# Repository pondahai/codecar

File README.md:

# codecar
programable toy car, Arduino + TAMIYA

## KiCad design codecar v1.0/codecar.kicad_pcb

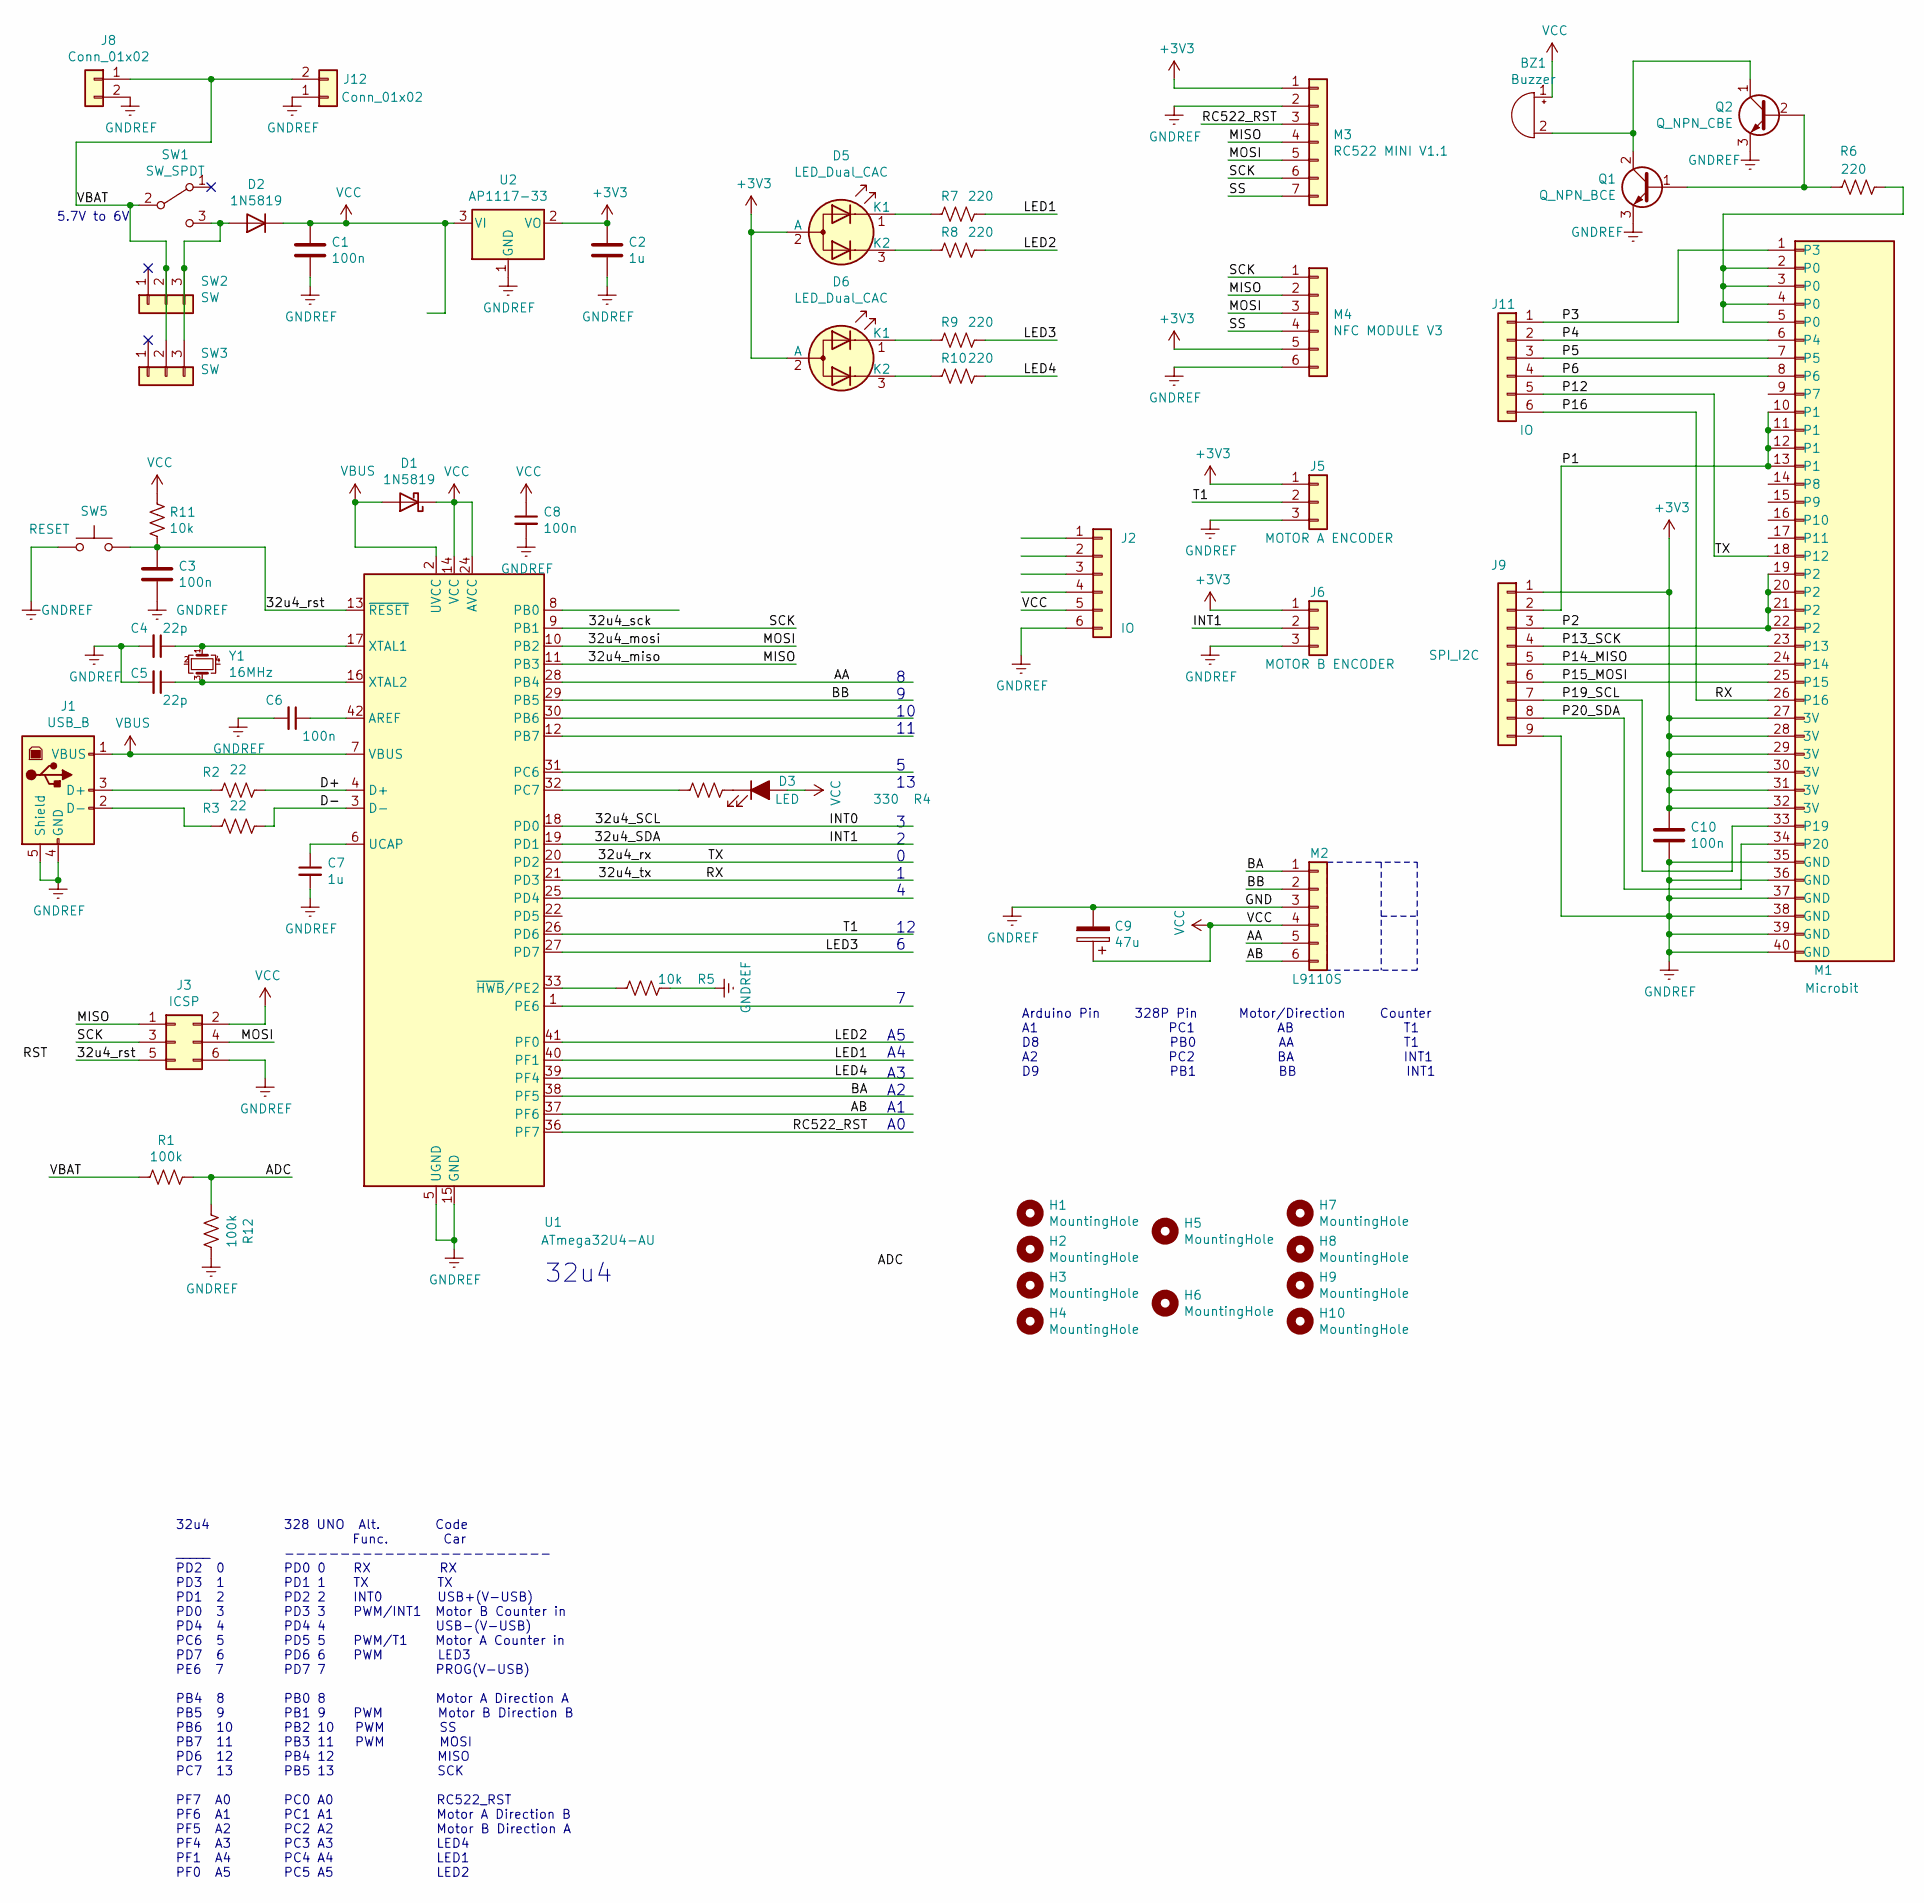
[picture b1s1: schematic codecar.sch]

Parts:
BZ1: Buzzer; Buzzer_12x9.5RM7.6
C1, C10: 100n; CP_EIA-2012-12_Kemet-R_Pad1.30x1.05mm_HandSolder
C2: 1u; C_Radial_D8.0mm_H7.0mm_P3.50mm
C3: 100n; CP_EIA-3216-10_Kemet-I_Pad1.58x1.35mm_HandSolder
C4, C5: 22p; C_0805_2012Metric
C6, C8: 100n; C_0805_2012Metric
C7: 1u; CP_EIA-3216-10_Kemet-I_Pad1.58x1.35mm_HandSolder
C9: 47u; C_Radial_D8.0mm_H7.0mm_P3.50mm
D1, D2: 1N5819; D_DO-41_SOD81_P10.16mm_Horizontal
D3: LED; LED_0805_2012Metric
D5, D6: LED_Dual_CAC; LED_D3.0mm-3
H1, H2, H3, H4: MountingHole; MountingHole_3.2mm_M3
H5, H6: MountingHole; MountingHole_4.3mm_M4
H7, H8, H9, H10: MountingHole; MountingHole_2.2mm_M2
J1: USB_B; USB_B_Lumberg_2411_02_Horizontal
J2, J11: IO; PinHeader_1x06_P2.54mm_Vertical
J3: ICSP; PinHeader_2x03_P2.54mm_Vertical
J5: MOTOR A ENCODER; TerminalBlock_Phoenix_MKDS-1,5-3_1x03_P5.00mm_Horizontal
J6: MOTOR B ENCODER; TerminalBlock_Phoenix_MKDS-1,5-3_1x03_P5.00mm_Horizontal
J8: Conn_01x02; Molex_KK-254_AE-6410-02A_1x02_P2.54mm_Vertical
J9: SPI_I2C; PinHeader_1x09_P2.54mm_Vertical
J12: Conn_01x02; TerminalBlock_Phoenix_MKDS-1,5-2_1x02_P5.00mm_Horizontal
M1: Microbit
M2: L9110S
M3: RC522 MINI V1.1; PinHeader_1x07_P2.54mm_Vertical
M4: NFC MODULE V3; PinHeader_1x06_P2.54mm_Vertical
Q1: Q_NPN_BCE; TO-92L_Inline_Wide
Q2: Q_NPN_CBE; TO-92L_Inline_Wide
R1, R12: 100k; R_0805_2012Metric
R2, R3: 22; R_0805_2012Metric
R4: 330; R_0805_2012Metric
R5: 10k; R_0805_2012Metric
R6: 220; R_0805_2012Metric
R7, R8, R9, R10: 220; R_0805_2012Metric_Pad1.20x1.40mm_HandSolder
R11: 10k; R_0805_2012Metric_Pad1.20x1.40mm_HandSolder
SW1: SW_SPDT; SW_Slide_1P2T_CK_OS102011MS2Q
SW2, SW3: SW; PinHeader_1x03_P2.54mm_Vertical
SW5: RESET; SW_PUSH_6mm_H5mm
U1: ATmega32U4-AU; TQFP-44_10x10mm_P0.8mm
U2: AP1117-33; SOT-223-3_TabPin2
Y1: 16MHz; Crystal_SMD_0603-4Pin_6.0x3.5mm_HandSoldering

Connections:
+3V3: C2.1, C10.1, D5.2 (A), D6.2 (A), J5.1, J6.1, J9.1, M1.27 (3V), M1.28 (3V), M1.29 (3V), M1.30 (3V), M1.31 (3V), M1.32 (3V), M3.1, M4.5, U2.2 (VO)
/32u4_SDA: J6.2, U1.19 (PD1)
/32u4_miso: J3.1, M3.4, M4.2, U1.11 (PB3)
/32u4_mosi: J3.4, M3.5, M4.3, U1.10 (PB2)
/32u4_rst: C3.1, J3.5, R11.2, SW5.2, U1.13 (~RESET)
/32u4_rx: J11.5, M1.18 (P12), U1.20 (PD2)
/32u4_sck: J3.3, M3.6, M4.1, U1.9 (PB1)
/32u4_tx: J11.6, M1.26 (P16), U1.21 (PD3)
/AA: M2.5, U1.28 (PB4)
/AB: M2.6, U1.37 (PF6)
/ADC: R1.1, R12.2
/BA: M2.1, U1.38 (PF5)
/BB: M2.2, U1.29 (PB5)
/D+: R2.1, U1.4 (D+)
/D-: R3.1, U1.3 (D-)
/LED1: R7.1, U1.40 (PF1)
/LED2: R8.1, U1.41 (PF0)
/LED3: R9.1, U1.27 (PD7)
/LED4: R10.1, U1.39 (PF4)
/P1: J9.2, M1.10 (P1), M1.11 (P1), M1.12 (P1), M1.13 (P1)
/P2: J9.3, M1.19 (P2), M1.20 (P2), M1.21 (P2), M1.22 (P2)
/P3: J11.1, M1.1 (P3)
/P4: J11.2, M1.6 (P4)
/P5: J11.3, M1.7 (P5)
/P6: J11.4, M1.8 (P6)
/P13_SCK: J9.4, M1.23 (P13)
/P14_MISO: J9.5, M1.24 (P14)
/P15_MOSI: J9.6, M1.25 (P15)
/P19_SCL: J9.7, M1.33 (P19)
/P20_SDA: J9.8, M1.34 (P20)
/RC522_RST: M3.3, U1.36 (PF7)
/SS: M3.7, M4.4
/T1: J5.2, U1.26 (PD6)
/VBAT: J8.1, J12.2, R1.2, SW1.2 (B), SW2.2, SW3.2
GNDREF: C1.2, C2.2, C3.2, C4.2, C5.2, C6.2, C7.2, C8.2, C9.2, C10.2, J1.4 (GND), J1.5 (Shield), J2.6, J3.6, J5.3, J6.3, J8.2, J9.9, J12.1, M1.35 (GND), M1.36 (GND), M1.37 (GND), M1.38 (GND), M1.39 (GND), M1.40 (GND), M2.3, M3.2, M4.6, Q1.3 (E), Q2.3 (E), R5.2, R12.1, SW5.1, U1.5 (UGND), U1.15 (GND), U1.23 (GND), U1.35 (GND), U1.43 (GND), U2.1 (GND)
unnamed: BZ1.2 (+), Q1.2 (C), Q2.1 (C)
unnamed: C4.1, U1.17 (XTAL1), Y1.1
unnamed: C5.1, U1.16 (XTAL2), Y1.3
unnamed: C6.1, U1.42 (AREF)
unnamed: C7.1, U1.6 (UCAP)
unnamed: D2.2 (A), SW1.3 (C), SW2.3, SW3.3
unnamed: D3.1 (K), R4.1
unnamed: D5.1 (K1), R7.2
unnamed: D5.3 (K2), R8.2
unnamed: D6.1 (K1), R9.2
unnamed: D6.3 (K2), R10.2
unnamed: J1.2 (D-), R3.2
unnamed: J1.3 (D+), R2.2
unnamed: M1.2 (P0), M1.3 (P0), M1.4 (P0), M1.5 (P0), R6.2
unnamed: Q1.1 (B), Q2.2 (B), R6.1
unnamed: R4.2, U1.32 (PC7)
unnamed: R5.1, U1.33 (~HWB~/PE2)
VBUS: D1.2 (A), J1.1 (VBUS), U1.2 (UVCC), U1.7 (VBUS)
VCC: BZ1.1 (-), C1.1, C8.1, C9.1, D1.1 (K), D2.1 (K), D3.2 (A), J2.5, J3.2, M2.4, R11.1, U1.14 (VCC), U1.24 (AVCC), U1.34 (VCC), U1.44 (AVCC), U2.3 (VI)

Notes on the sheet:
5.7V to 6V
Arduino Pin 328P Pin Motor/Direction Counter A1 PC1 AB T1 D8 PB0 AA T1 A2 PC2 BA INT1 D9 PB1 BB INT1
328 UNO Alt. Code Func. Car ------------------------ PD0 0 RX RX PD1 1 TX TX PD2 2 INT0 USB+(V-USB) PD3 3 PWM/INT1 Motor B Counter in PD4 4 USB-(V-USB) PD5 5 PWM/T1 Motor A Counter in PD6 6 PWM LED3 PD7 7 PROG(V-USB) PB0 8 Motor A Direction A PB1 9 PWM Motor B Direction B PB2 10 PWM SS PB3 11 PWM M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
A3 A2 A1 A0
A5 A4
8 9 10 11
5 13
12 6
3 2 0 1 4
32u4 _____ PD2 0 PD3 1 PD1 2 PD0 3 PD4 4 PC6 5 PD7 6 PE6 7 PB4 8 PB5 9 PB6 10 PB7 11 PD6 12 PC7 13 PF7 A0 PF6 A1 PF5 A2 PF4 A3 PF1 A4 PF0 A5
32u4

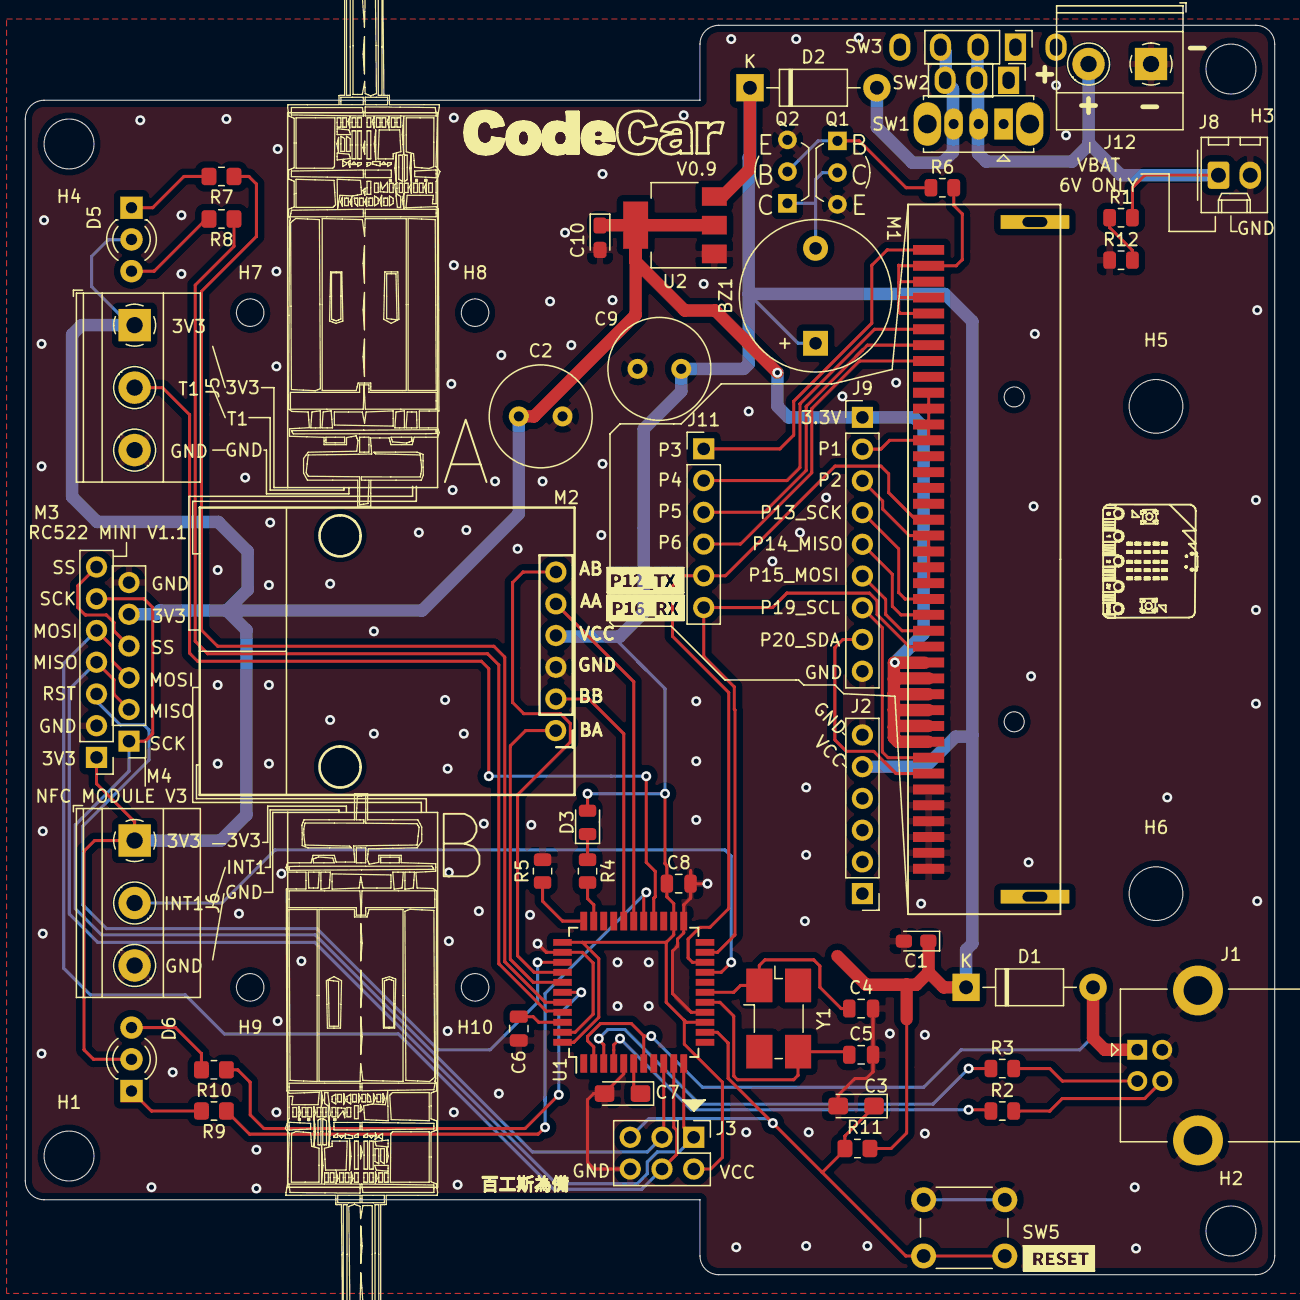
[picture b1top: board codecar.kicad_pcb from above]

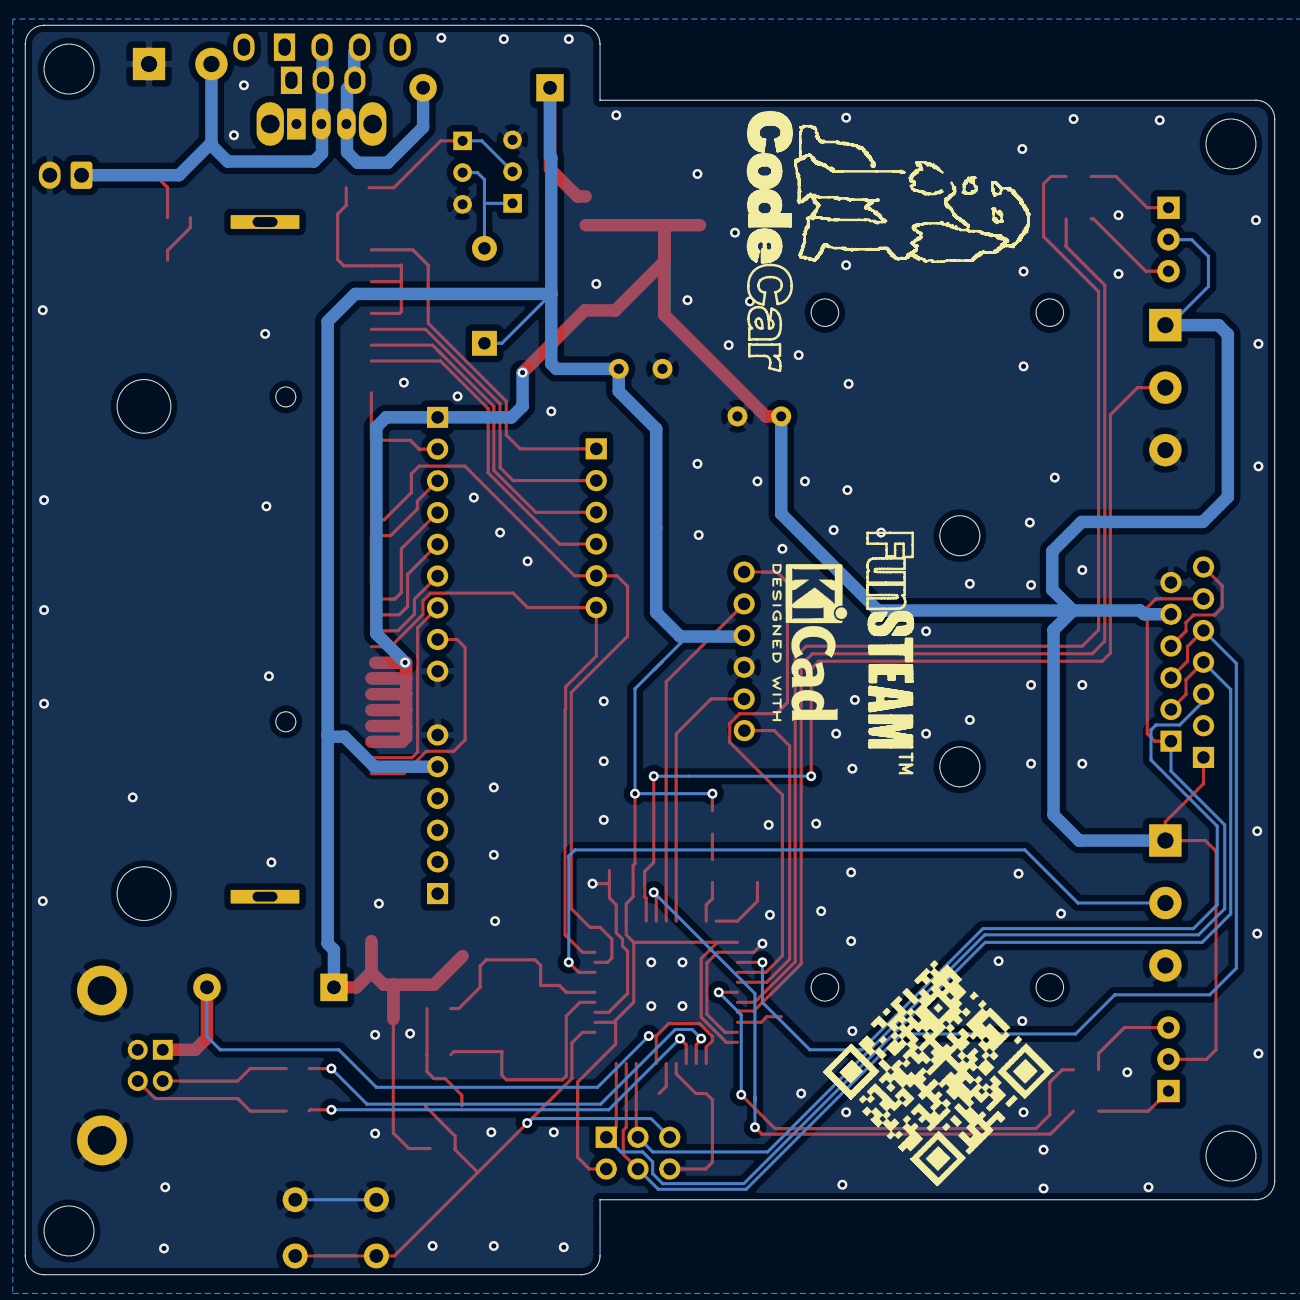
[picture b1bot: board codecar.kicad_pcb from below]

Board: 2 copper layers, 100.0 x 100.0 mm, 64 parts (3 on the bottom side), 54 nets.

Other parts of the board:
LOGO1, LOGO1#2: CodeCar_Logo
LOGO1#3: KiCad-Logo2_5mm_SilkScreen
LOGO2: funsteam_logo

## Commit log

2016-08-02 init
2017-10-06 minor
2021-06-28 Rename pitches.h to software/pitches.h
2021-06-28 Rename codecar.ino to software/codecar.ino
2021-06-28 refine
